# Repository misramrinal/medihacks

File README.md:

# Medihacks

## Launching
### In order to run the website
```bash
python login.py
```
Then click on the link provided in the terminal
```bash
http://127.0.0.1:5000
```
This will launch the website. In order to check your fitness, first login with your username and password and then click on Check your fitness button. This will take you to a page which will show you the live sensor data along with your stress level and fitness index prediction and you can also see your BMI index

Or you an directly visit this link where we have hosted our website
```bash
https://misramrinal.pythonanywhere.com/
```

This project aims at developing an innovative solution that uses non-invasive methods or facial reading technologies to collect health vitals and derive a fitness score that is accurate, reliable, scalable, and can be deployed in various settings, from individual homes to large healthcare organizations.The model has an accuracy of 94%.

Our solution approach is:

- Collection of health data from multiple sensors like heart rate sensor[MAX30100](https://www.googleadservices.com/pagead/aclk?sa=L&ai=DChcSEwiBwtSgl5OAAxVokmYCHayHARYYABADGgJzbQ&ae=2&ohost=www.google.com&cid=CAESbeD24wXBk5ZzJFf2u8SABNRn9sXr6rfA9lxRIw6pJDPRrm0YF-2hxxY0dIUxZqDdhSeYgL-WT3kGR5HcEi2M3wqlTsLS1hauIALa5dBEvMEIMQLdFRuNWlTGGSYd0jCW9pT9S3PNhVb0ESJ-XLM&sig=AOD64_0GYnq2_s3afIoi7u4te_2mJRxxEA&ctype=5&q=&ved=2ahUKEwi068qgl5OAAxU1amwGHRNZDyUQ9aACKAB6BAgGEBU&adurl=), accelerometer[(MPU6050)](https://robu.in/product/mpu-6050-gyro-sensor-2-accelerometer/), [ESP-32 CAM Wifi Module](https://www.electronicscomp.com/esp32-cam-wifi-module-bluetooth-with-ov2640-camera-module-2mp-for-face-recognization?gclid=Cj0KCQjwqs6lBhCxARIsAG8YcDjopqELU-LpxUKawFz5oCwQjMG2bDbsRsNPxCS4mywbILHjh4zcjdAaAliMEALw_wcB), [blood glucose sensor](https://www.researchgate.net/figure/Working-principle-of-the-glucose-sensor-patch-and-characterization-in-a-semi-infinite_fig1_358801890) and [temperature sensor](https://eepower.com/resistor-guide/resistor-types/ntc-thermistor/)
- Storing data on Firebase database

- Data analyis and training using several ML Algorithms
- Model Deployment 

## Optimizations
- hyperparameters tuned in MLP Classifier.

## Screenshots

Web page

## Situps
https://github.com/misramrinal/medihacks/assets/100671634/60e564a8-ab07-41e6-99f4-5f3613cb7943

## Pushups
https://github.com/misramrinal/medihacks/assets/100671634/ef5d65f9-eb93-4305-9312-cddb05f4a654

## Roadmap

## PCB design of Smart Watch

## Tools and Tech Stacks
- Flask
- Numpy
- Pandas
- Matplotlib
- sklearn
- Firebase
- Arduino
- Mediapipe
- Eagle
- HTML, CSS, javascript, bootstrap

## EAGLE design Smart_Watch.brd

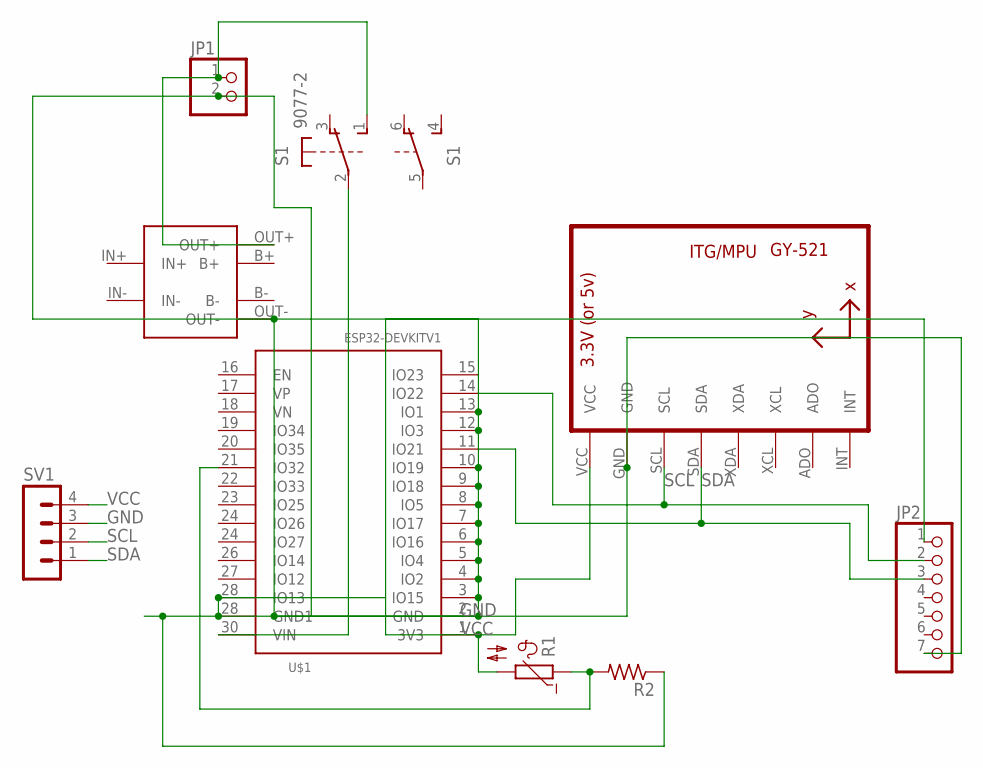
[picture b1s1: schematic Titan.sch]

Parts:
JP1: PINHD-1X2; 1X02
JP2: PINHD-1X7; 1X07
R1: NTC640; P640
R2: R-US_0207/10; 0207/10
S1: 9077-2
SV1: MA04-1
U1: GY-521MPU6050; GY-521
U$1: ESP32DEVKITV1; ESP32-DEVKITV1
U$3: TP4056

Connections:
GND: JP1.2, JP2.7, R2.1, SV1.3, U1.GND, U$1.2 (GND), U$1.3 (IO15), U$1.4 (IO2), U$1.5 (IO4), U$1.6 (IO16), U$1.7 (IO17), U$1.8 (IO5), U$1.9 (IO18), U$1.10 (IO19), U$1.12 (IO3), U$1.13 (IO1), U$1.28 (IO13), U$3.OUT-
unnamed: U1.INT, U$1.15 (IO23)
unnamed: JP1.1, S1.1 (S), U$3.OUT+
unnamed: R1.1, R2.2, U$1.21 (IO32)
unnamed: S1.2, U$1.30 (VIN)
SCL: JP2.2, SV1.2, U1.SCL, U$1.14 (IO22)
SDA: JP2.3, SV1.1, U1.SDA, U$1.11 (IO21)
VCC: JP2.1, R1.2, SV1.4, U1.VCC, U$1.1 (3V3)

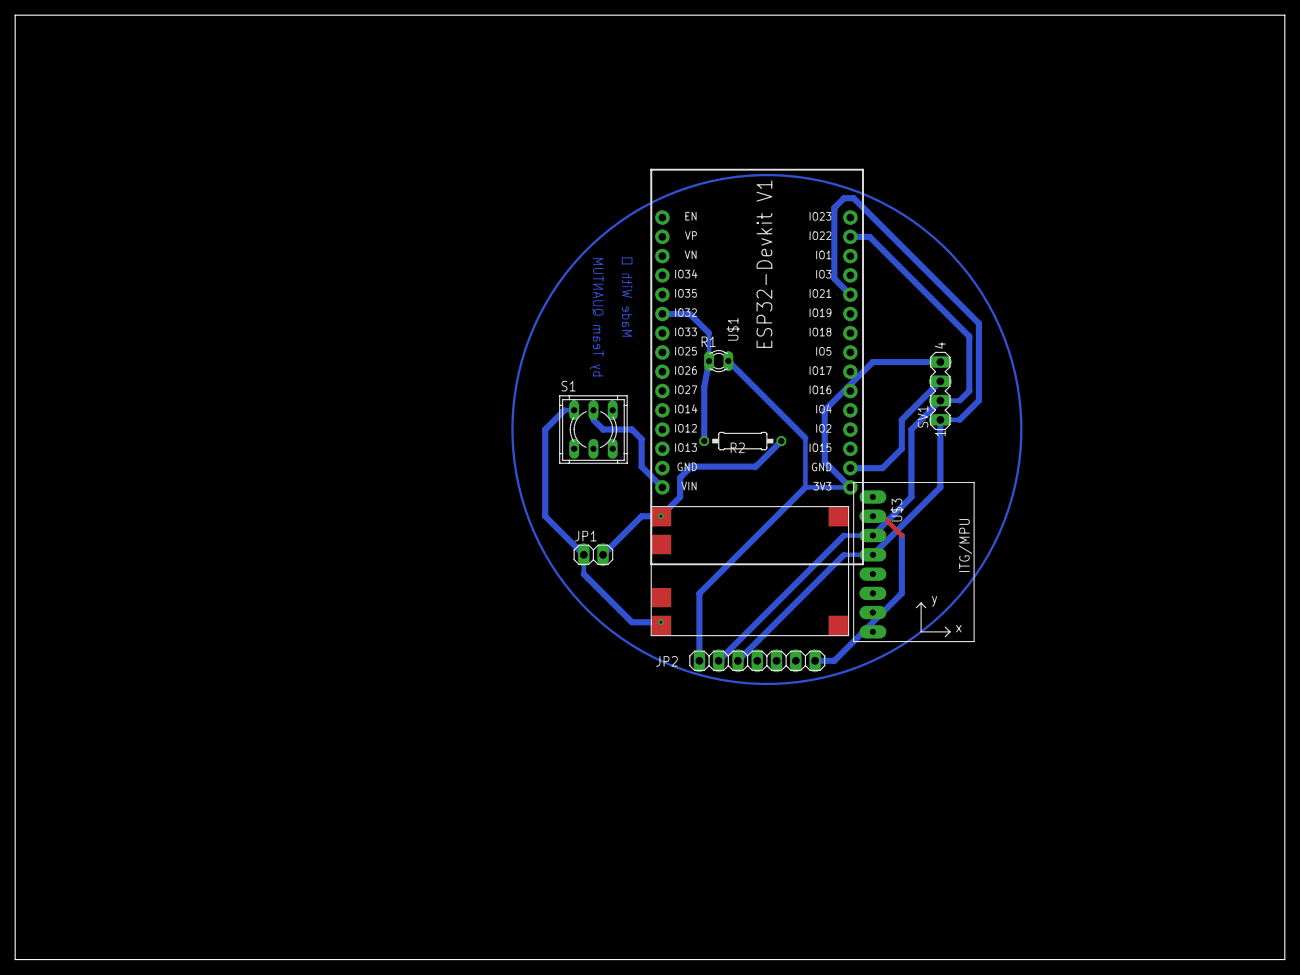
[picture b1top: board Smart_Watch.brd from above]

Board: 2 copper layers, 167.3 x 124.4 mm, 9 parts (0 on the bottom side), 8 nets.

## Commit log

2023-09-09 added required datasheet and model
    took the datasheet that was best for our purpose from kaggle and trained a model on it to find the fitness score
2023-09-09 created the required .pkl files
2023-09-09 added some bootstrap and css
2023-09-09 added css, bootstrap, js
2023-09-09 added assets
2023-09-09 updated assets
2023-09-09 added base template
2023-09-09 added login page
2023-09-09 added webpage
    added webpage for testing the output of pushup.py and situp.py
2023-09-09 added mediapipe script
    added pushup counter and situp counter
2023-09-09 added webpage for testing situp counter
2023-09-09 Testing code for deploying webpage using flask
2023-09-09 Add files via upload
    Added PCB schematic of smart watch
2023-09-09 Added PCB Schematic of Smart Watch
2023-09-09 Main launch code
2023-09-09 Add files via upload
    Added PCB board design of Smart Watch
2023-09-09 Added PCB board design of Smart Watch
2023-09-09 Added comments for readability
2023-09-10 updated changes
2023-09-10 updated webpage
